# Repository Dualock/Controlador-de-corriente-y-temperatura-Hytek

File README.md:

# Diseño e implementación un controlador de corriente y temperatura para diodos láseres de alta corriente (> 1A) con tecnología Hytek, un sistema embebido de bajo costo e interfaz gráfica para el usuario.

Repositorio para agregar documentación, referencias y código del proyecto eléctrico

# Integrantes:
* Dualock Fonseca Monge
* Gokeh Ávila Blanco

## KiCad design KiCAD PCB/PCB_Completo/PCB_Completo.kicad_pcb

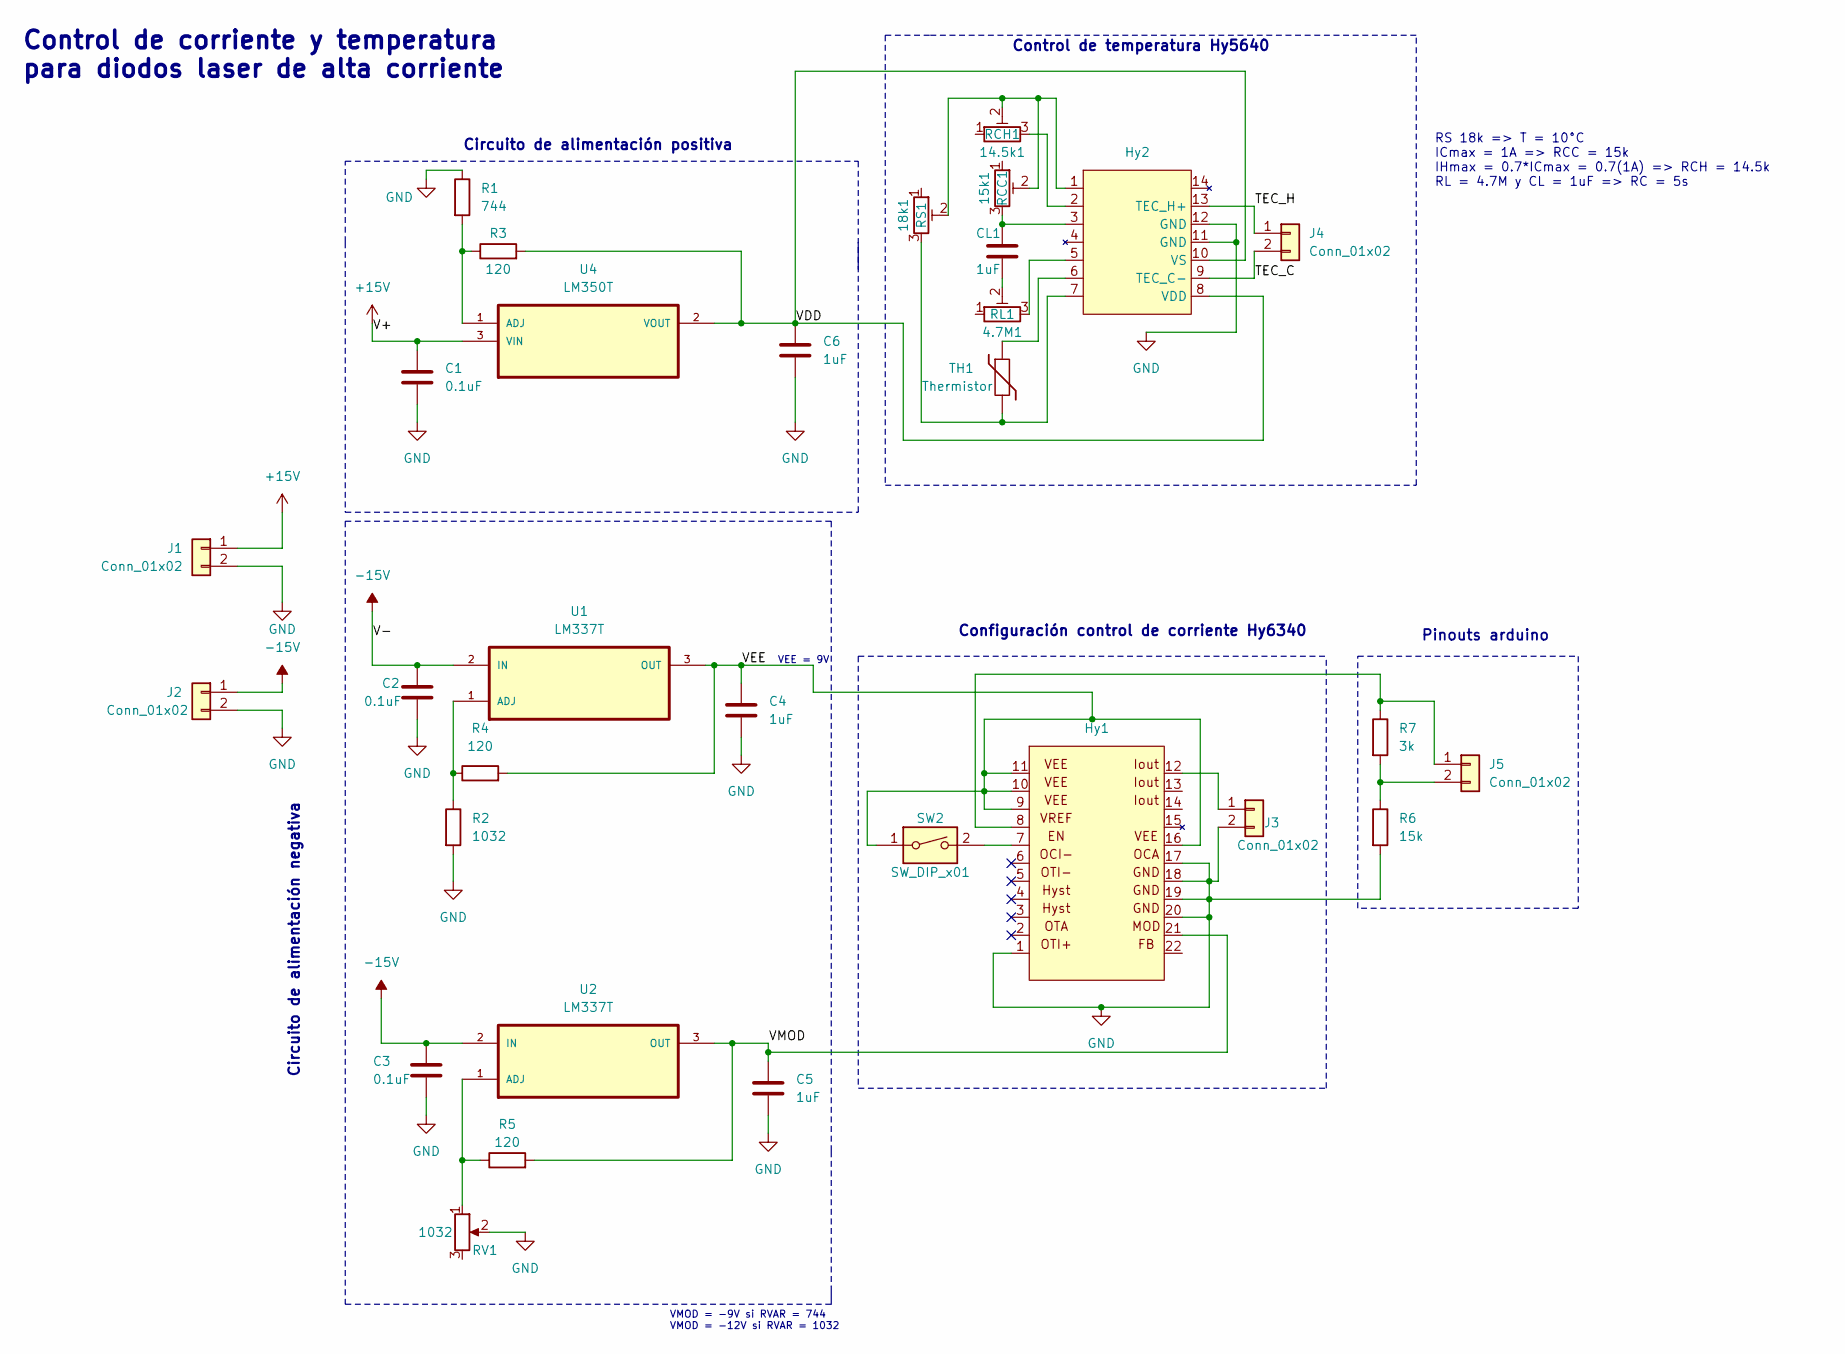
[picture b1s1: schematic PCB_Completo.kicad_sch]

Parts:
C1, C2, C3: 0.1uF; C_Axial_L3.8mm_D2.6mm_P7.50mm_Horizontal
C4, C5, C6: 1uF; C_Axial_L3.8mm_D2.6mm_P7.50mm_Horizontal
CL1: 1uF; C_Axial_L3.8mm_D2.6mm_P7.50mm_Horizontal
Hy1: Hy6340
Hy2: Hy5640
J1, J2, J3, J4, J5: Conn_01x02; JWT_A3963_1x02_P3.96mm_Vertical
R1: 744; R_Axial_DIN0207_L6.3mm_D2.5mm_P15.24mm_Horizontal
R2: 1032; R_Axial_DIN0207_L6.3mm_D2.5mm_P15.24mm_Horizontal
R3, R4, R5: 120; R_Axial_DIN0207_L6.3mm_D2.5mm_P15.24mm_Horizontal
R6: 15k; R_Axial_DIN0207_L6.3mm_D2.5mm_P15.24mm_Horizontal
R7: 3k; R_Axial_DIN0207_L6.3mm_D2.5mm_P15.24mm_Horizontal
RCC1: 15k1; Potentiometer_Bourns_3296W_Vertical
RCH1: 14.5k1; Potentiometer_Bourns_3296W_Vertical
RL1: 4.7M1; Potentiometer_Bourns_3296W_Vertical
RS1: 18k1; Potentiometer_Bourns_3296W_Vertical
RV1: 1032; Potentiometer_Bourns_3296W_Vertical
SW2: SW_DIP_x01; SW_DIP_SPSTx01_Slide_6.7x4.1mm_W7.62mm_P2.54mm_LowProfile
TH1: Thermistor; R_0805_2012Metric_Pad1.20x1.40mm_HandSolder
U1, U2: LM337T; TerminalBlock_Philmore_TB133_1x03_P5.00mm_Horizontal
U4: LM350T; TerminalBlock_MetzConnect_Type094_RT03503HBLU_1x03_P5.00mm_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

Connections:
+15V: C1.1, J1.1, U4.3 (VIN)
-15V: C2.1, C3.1, J2.1, U1.2 (IN), U2.2 (IN)
/TEC_C: Hy2.9 (TEC_C-), J4.2
/TEC_H: Hy2.13 (TEC_H+), J4.1
/VDD: C6.1, Hy2.8 (VDD), Hy2.10 (VS), R3.2, U4.2 (VOUT)
/VEE: C4.1, Hy1.9, Hy1.10, Hy1.11, Hy1.16, R4.2, SW2.1, U1.3 (OUT)
/VMOD: C5.1, Hy1.21, R5.2, U2.3 (OUT)
GND: C1.2, C2.2, C3.2, C4.2, C5.2, C6.2, Hy1.1, Hy1.17, Hy1.18, Hy1.19, Hy1.20, Hy2.11 (GND), Hy2.12 (GND), J1.2, J2.2, J3.2, R1.1, R2.2, R6.2, RV1.2
unnamed: CL1.1, Hy2.3, RCC1.3
unnamed: CL1.2, RL1.2
unnamed: Hy1.7, SW2.2
unnamed: Hy2.1, RCC1.2, RCH1.2, RS1.2
unnamed: Hy2.2, RCH1.3
unnamed: Hy2.5, RL1.3
unnamed: Hy2.6, TH1.1
unnamed: Hy2.7, RS1.3, TH1.2
unnamed: Hy1.12, J3.1
unnamed: Hy1.8, J5.1, R7.1
unnamed: J5.2, R6.1, R7.2
unnamed: R2.1, R4.1, U1.1 (ADJ)
unnamed: R5.1, RV1.1, U2.1 (ADJ)
unnamed: R1.2, R3.1, U4.1 (ADJ)

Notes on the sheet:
VMOD = -9V si RVAR = 744 VMOD = -12V si RVAR = 1032
Control de corriente y temperatura para diodos laser de alta corriente
Circuito de alimentación positiva
Circuito de alimentación negativa
RS 18k => T = 10°C ICmax = 1A => RCC = 15k IHmax = 0.7*ICmax = 0.7(1A) => RCH = 14.5k RL = 4.7M y CL = 1uF => RC = 5s
VEE = 9V
Control de temperatura Hy5640
Pinouts arduino
Configuración control de corriente Hy6340

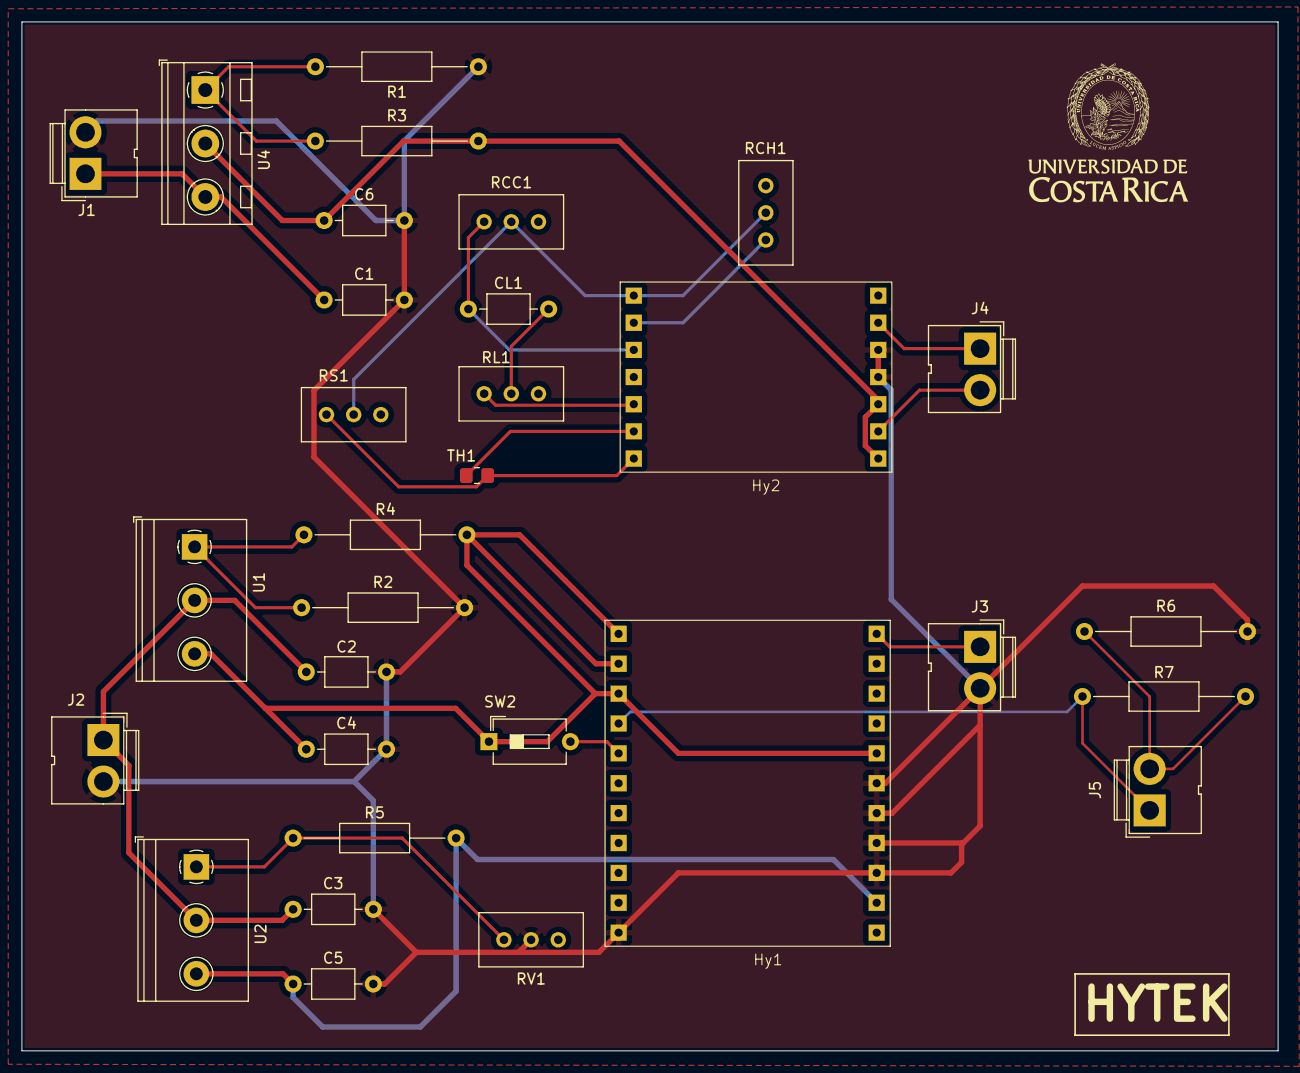
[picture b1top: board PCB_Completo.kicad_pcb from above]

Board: 2 copper layers, 117.5 x 96.2 mm, 31 parts (0 on the bottom side), 22 nets.

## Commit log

2023-09-10 Referencias y hojas de datos
    Se agregan las hojas de datos de ambos controladores y material de referencia extra
2023-09-29 Avance semana 7
2023-10-04 Actualizacion de archivos
    El último commit no tenía los actualizados.
2023-10-13 Actualización
    Diseños preliminares de ambos circuitos
2023-10-21 Actualización
2023-10-23 Add files via upload
    Se agrega pdf del diseño del circuito completo
2023-10-23 Add files via upload
    Agrega circuito con conexiones utilizando tinkercad
2023-10-23 Add files via upload
    Se agrega el circuito completo en KiCAD
2023-10-30 Add files via upload
    Se agrega hoja de datos del regulador de tension para tensiones positivas LM350
2023-11-03 Actualización y corrección de errores
2023-11-12 Add files via upload
    Se agrega avance del PCB
2023-11-13 Actualización del esquemático
2023-11-13 Rename Readme.md.txt to Readme.md
    Corrección de error de formato
2023-11-14 Interfaz_temperatura
2023-11-14 Imagen de divisor de tensiones
2023-11-30 Update Readme.md
    Se agrega la documentación de la interfaz para sensar corriente
2023-11-30 Update Readme.md
    Fixing a minor error
2023-12-01 Interfaz_Sensor_corriente
2023-12-01 Images name changing
2023-12-02 Se agrega el PCB completo
2023-12-02 Se agregan las imagenes del diseño mas actualizado y el pcb
2023-12-02 Update Readme.md
    Readme typo
2023-12-04 Entregables
2023-12-04 Bitácora Semana 7
2023-12-04 Presentación de avance
